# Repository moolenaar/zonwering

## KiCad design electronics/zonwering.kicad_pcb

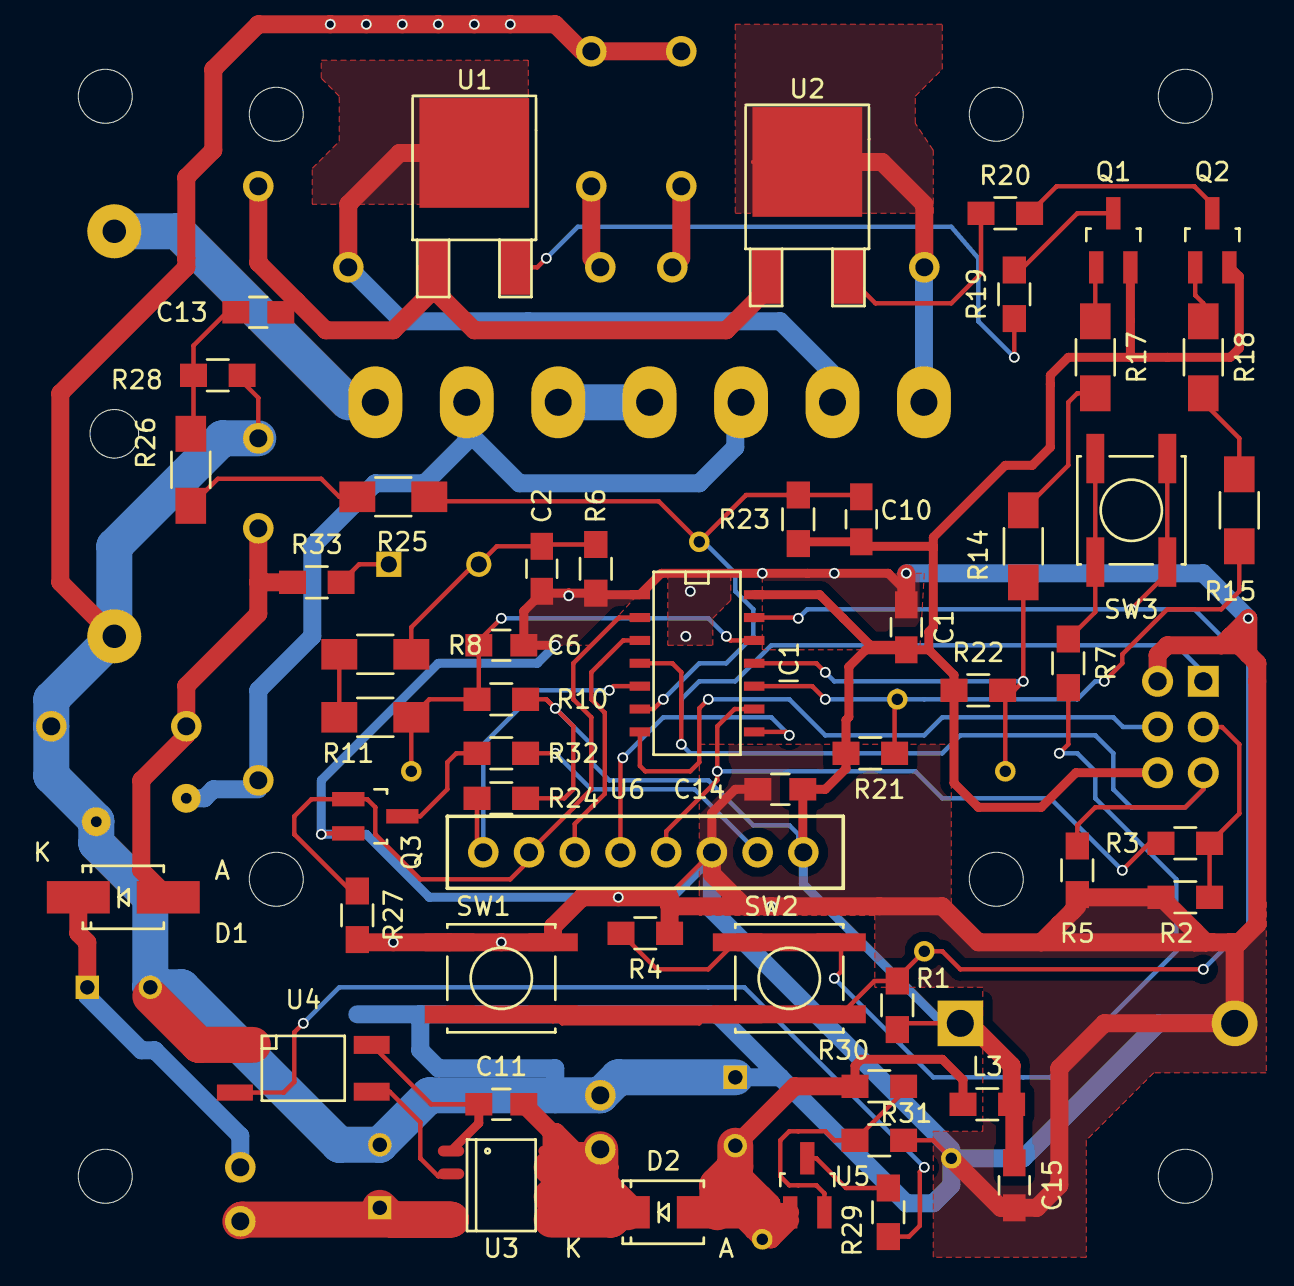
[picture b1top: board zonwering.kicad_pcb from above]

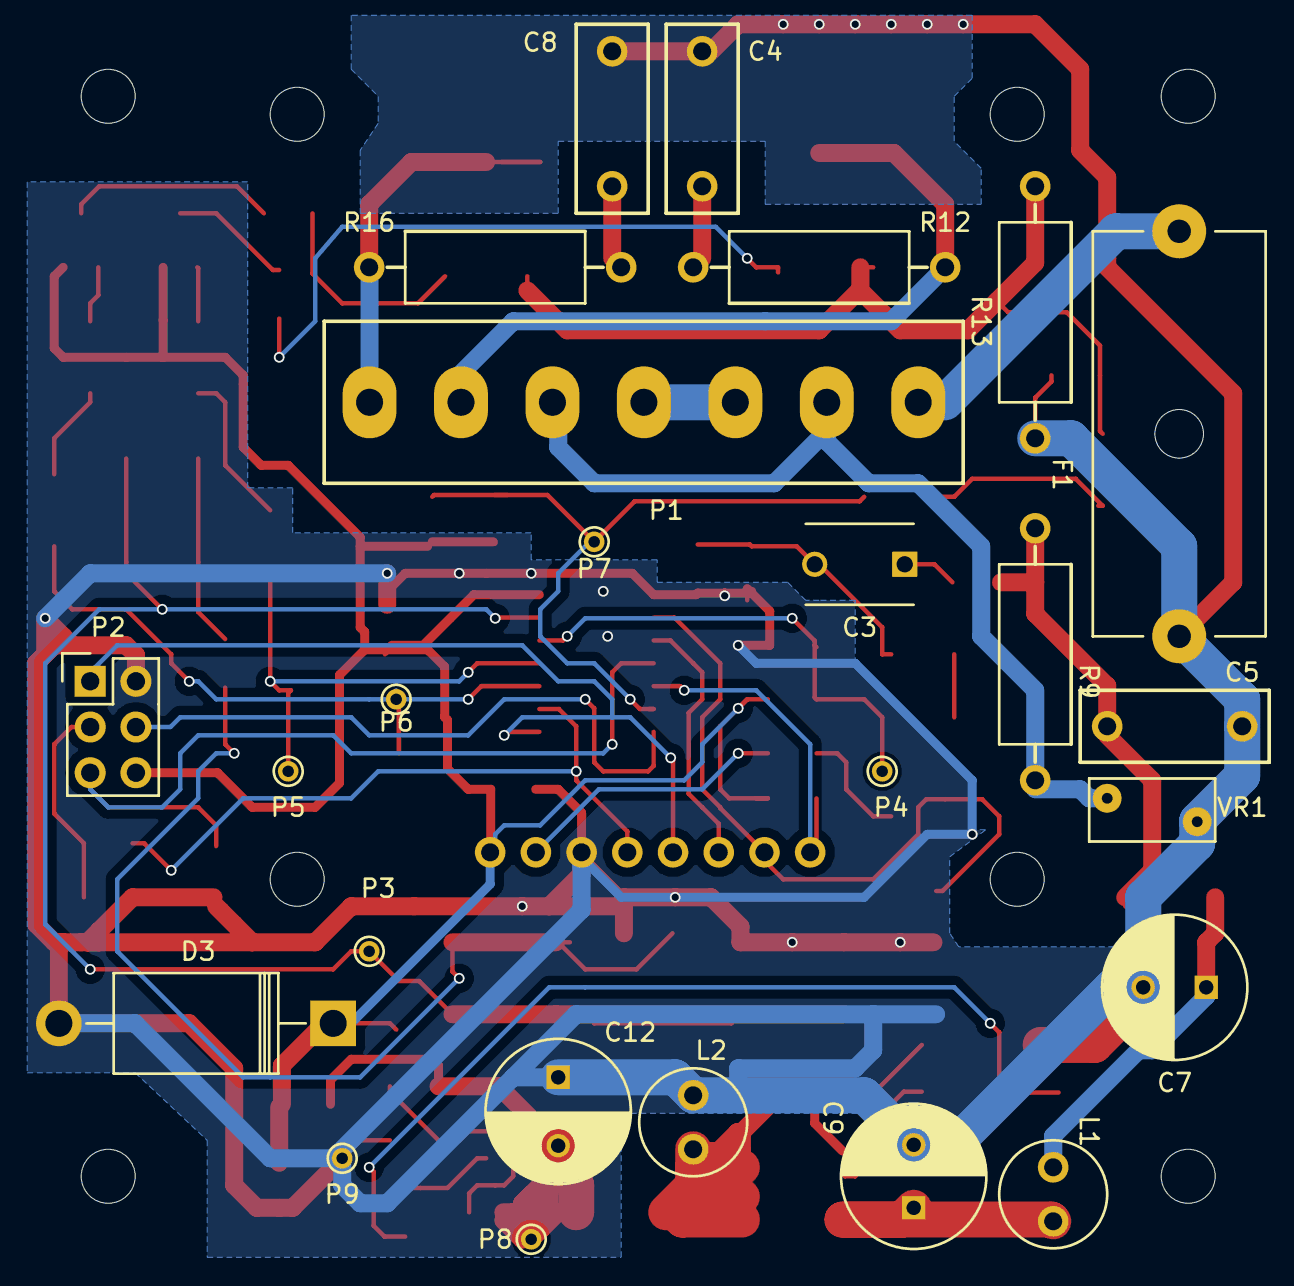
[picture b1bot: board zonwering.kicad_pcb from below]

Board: 2 copper layers, 82 parts (25 on the bottom side), 50 nets.

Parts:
C1, C11, C13, C14: 100nF; C_0805_HandSoldering
C2: 150nF; C_0805_HandSoldering
C3: 470pF; C_Disc_D6_P5
C4, C5, C8: 10nF; capacitor_RM7.5
C6, C10: 100pF; C_0805_HandSoldering
C7, C9: 2.2uF; C_Radial_D8_L11.5_P3.5
C12: 100uF; C_Radial_D8_L13_P3.8
C15: 1uF; C_0805_HandSoldering
D1, D2: US1M; SMA_Handsoldering
D3: ZD 5W 4,7V; Diode_DO-201AD_Horizontal_RM15
F1: 1A slow; Fuseholder5x20_horiz_open_Schurter_0031_8201
IC1: ATTINY84S; SOIC-14_N
L1: 100uH; Choke_6mm
L2: 1mH; Choke_6mm
L3: 10uH; R_0805_HandSoldering
P1: CONN_01X07; Power_connector_Straight_508_7pin
P2: CONN_02X03; Pin_Header_Straight_2x03
P3: key; PINTST
P4: mains; PINTST
P5: down; PINTST
P6: up; PINTST
P7: sense; PINTST
P8: -3.3V; PINTST
P9: 0V; PINTST
Q1, Q2: BSS138; SOT-23_Handsoldering
Q3: OA3401A; SOT-23_Handsoldering
R1, R2, R21, R22, R24, R27: 100k; R_0805_HandSoldering
R3, R5: 4.7k; R_0805_HandSoldering
R4, R7, R30: 47k; R_0805_HandSoldering
R6, R10, R23, R28: 1M; R_0805_HandSoldering
R8, R11, R14, R15, R17, R18, R25, R26: 100k; R_1206_HandSoldering
R9: 47; Resistor_14mm
R12, R16: 2.2k; Resistor_14mm
R13: 1; Resistor_14mm
R19, R20, R33: 100; R_0805_HandSoldering
R29: 10; R_0805_HandSoldering
R31: 12k; R_0805_HandSoldering
R32: 22; R_0805_HandSoldering
REF1, REF2, REF3, REF4: MountingHole_3mm
SW1, SW2, SW3: tactile switch; SW_SPST_EVPBF
U1, U2: BT137S-600E; TO-252-2Lead
U3: LNK302D; SO-8C
U4: PC817; Optocoupler_SMD_HandSoldering_KPC357_LTV35x_PC357_SingleCha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
U5: TL431; SOT-23_Handsoldering
U6: LCD5110; Nokia_lcd5110
VR1: JVR7N391K; RV_Disc_D7_W3.5_P5

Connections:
-3V3: C1.2, C10.2, C14.2, C15.1, D3.1, IC1.14, L3.2, P2.6, Q1.2, Q2.2, R1.2, R10.2, R21.1, R22.1, R23.2, R24.2, U6.8
/CLK: P2.3, R2.2, R3.2
/MOSI: IC1.7, P2.4
/RST: IC1.4, P2.5, R5.2
D/nC: IC1.3, U6.3
DOWN: R19.1, U1.3
GND: C1.1, C2.1, C4.2, C5.2, C6.1, C7.2, C8.2, C9.2, C12.1, C14.1, C15.2, D3.2, F1.1, IC1.1, L2.1, P2.2, P9.1, Q3.2, R2.1, R4.2, R5.1, R6.1, R13.2, R27.1, R28.2, R31.2, SW1.1, U4.1, U6.6, VR1.2
LCDCLK: IC1.9, R3.1, U6.5
LCDDin: IC1.8, P2.1, U6.4
unnamed: C2.2, C3.2, R6.2, R8.2
unnamed: C3.1, R33.2
unnamed: C4.1, R12.2
unnamed: C5.1, D1.2, R9.1, R33.1
unnamed: C6.2, IC1.12, P4.1, R10.1, R11.1
unnamed: C7.1, D1.1, L1.1
unnamed: C8.1, R16.2
unnamed: C9.1, L1.2, U3.4
unnamed: C10.1, IC1.6, P7.1, R23.1, R25.2
unnamed: C11.1, U3.1, U4.4
unnamed: C11.2, D2.1, L2.2, U3.5, U3.6, U3.7, U3.8
unnamed: C12.2, D2.2, L3.1, P8.1, R30.1, U5.1
unnamed: C13.2, R26.1, R28.1
unnamed: F1.2, P1.1
unnamed: IC1.10, P6.1, R15.2, R21.2
unnamed: IC1.11, P5.1, R14.2, R22.2
unnamed: IC1.13, P3.1, R1.1, SW1.2, SW2.2, SW3.2
unnamed: P1.2, P1.5, R9.2, VR1.1
unnamed: P1.3, P1.4
unnamed: P1.6, R12.1, U1.2
unnamed: P1.7, R16.1, U2.2
unnamed: Q1.1, R17.1
unnamed: Q1.3, R19.2
unnamed: Q2.1, R18.1
unnamed: Q2.3, R20.2
unnamed: Q3.3, R32.1
unnamed: R4.1, R7.2, SW2.1
unnamed: R7.1, SW3.1
unnamed: R8.1, R11.2
unnamed: R14.1, R17.2
unnamed: R15.1, R18.2
unnamed: R25.1, R26.2
unnamed: R29.1, U4.2
unnamed: R29.2, U5.3
unnamed: R30.2, R31.1, U5.2
unnamed: R32.2, U6.7
unnamed: U3.2, U4.3
SENSE: C13.1, R13.1, U1.1, U2.1
UP: R20.1, U2.3
nCE: IC1.2, Q3.1, R27.2, U6.2
nRESET: IC1.5, R24.1, U6.1

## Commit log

2020-01-05 first checkin status: changes in schematic, PCB need to be updated software changed for testing ADC
2020-01-06 separate file for each screen in the UI
2020-01-10 new way of handling key presses progress bar jumps
2020-01-14 motor control works, open / close timer works, key press works todo: eeprom storage, automatic closing timer and seeting value for fully open
2020-01-15 improved behaviour, code cleanup. flash is almost full
2020-01-16 pressing up key when moving down stops motor
2020-01-16 added fully open screen
2020-01-17 Improved behavior of the UI
2020-01-18 - eeprom storage (not finished) - optimization except for the kernel
2020-01-18 store settings in eeprom
2020-01-18 Added idle screen and switch off backlight when not in use
2020-01-18 - code cleanup - added ":" character and deleted "." character (6x10 font) - delay count start at 30 (instead of 29) - store setpoint in eeprom
2020-01-18 should be part of previous checkin
2020-01-19 removed current measurement noticed that, after programming, the checksum of the parameters is rejected
2020-01-28 added front side of enclosure; not good
2020-02-01 corrected position of lcd window, rounded front edges, still not ok
2020-02-02 front and button ok, bottom plate not finished
2020-05-24 - 600v triac was not enough - increased additional closing time
2020-05-30 - closing takes 10% longter then opening - additional closing time 500ms
